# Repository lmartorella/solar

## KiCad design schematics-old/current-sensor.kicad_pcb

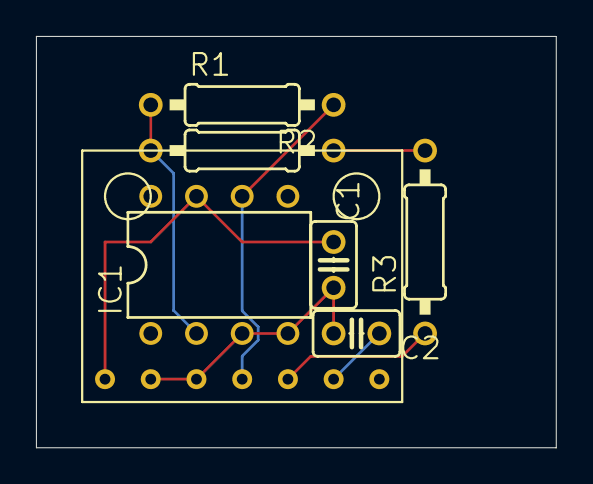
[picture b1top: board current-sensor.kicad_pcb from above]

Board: 2 copper layers, 28.9 x 22.9 mm, 7 parts (0 on the bottom side), 7 nets.

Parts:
C1: 100n; C025-025X050
C2: 1u; C025-025X050
IC1: 741P; DIL08
R1: 81k; 0207_10
R2: 33k; 0207_10
R3: 39; 0207_10
U$1: LTC1966_MODULE

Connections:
+5V: C1.1, IC1.7, U$1.P$1
GND: C1.2, C2.2, IC1.3, IC1.4, U$1.P$2, U$1.P$3
unnamed: C2.1, U$1.P$6
unnamed: IC1.2, R1.1, R2.2
unnamed: IC1.6, R1.2, U$1.P$4
unnamed: R2.1, R3.2
unnamed: R3.1, U$1.P$5

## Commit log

2019-04-23 - Restructuring folders to split app from lib
2019-04-24 Moved solution out
2019-04-24 Refactored done and working
2019-04-26 - Refactoring with dll reflection load done
2019-05-15 - Removed sink tabs without UI - Added some inline doc on classes - Code cleanup
2019-05-16 - Refactoring the web server - Added default garden cfg writer - Moved samples and webapp outside web code - Code simplification - Moved plotly and require to npm - Converted server code back to JS
2019-05-17 - Documenting
2019-07-03 - Added doc for ubean - Documenting
2020-03-23 - Added digital input simulator and tester device
2020-03-23 - Fixed serialization of JSON - Added node removal from simulator UI - Fixed UT
2020-03-23 - Fixed logger device - Added Initialized async task in Sinks
2020-03-23 - Implemented flow reading from bus
2020-03-24 - Implemented simulator too - Temp: update flow on web request
2020-03-25 - Fixed digio hw and c# sink driver
2020-03-28 Migrated to VS2019 and .NET 4.7.2
2020-03-31 - Admim mail support - Added packaging and install - Various web fixes
2020-04-04 - Added pump logger - Refactored the big Garden device file in sub classes
2020-04-04 - Fixed process management after restart
2020-04-05 - I18N of the web GUI
2020-04-07 - Protocol webserver/server reworked - .NET message separation samples/core
2020-04-07 - Completed localization
2020-04-07 - Better mail report (text) - Added Night Mode switch in the simulator - Added protocol debug
2020-04-07 - Completed loaded async reaction - Fixed daylight management after restart
2020-04-13 - Fixed JSON serialization ploymorphism - Fixed solar exception - Fixed i18n
2020-04-13 Merged schematics repo
2020-04-13 Current sensor
2020-04-13 - Sensor board
2020-04-13 - Fixed solar TCP open/close loop - Added logs to listen socket issue on raspbian (missing POLLINVALID check?)
2020-04-18 - i18n in garden
2020-04-21 Reworking disabled, to introduce suspend
2020-04-22 - Added suspended and reminder mail
2020-04-22 - Done
2020-04-26 - Integrated power usage reading in solar power to calculate Net Energy Meter
2020-04-27 - Added suspend/resume UI
2020-04-27 - WIP editor for cycles
2020-04-28 - Working editor for cycles
2020-04-29 - Resume from rain now updates the start time
2020-04-29 - Better implementation of remote set config
2020-04-29 - Hide Stop command if not running
2020-04-29 - Added login precheck
2020-04-29 - Fixed unhanlded
2020-04-29 - Fixed next cycle calculation after rain
2020-05-01 - Refactored zone names managements
2020-05-03 - Clean up immediate, now single cycle
2020-05-03 - Introduced optional sinks
2020-05-07 - Send restart mail with exception stack
2020-05-08 - Show current usage in W
2020-05-10 - Fixed deserialization buffer underflow management: TCP connection must be closed in that case to allow subsequent node access
2021-01-06 - SAMIL: New error code witnessed
2021-05-18 - More detailed errors about inverter packet errors
2021-05-22 - Support for 'broken' undocumented checksum?
2022-10-20 - Added scripts to aggregate yearly solar data
2023-05-14 - Folder renamed - Removed old PIC targets - Fixed UTs
2023-05-14 - Adding common service to replace the in-memory IPC pipe with the web gui
2023-05-14 - To test
2023-05-14 - Converted named pipe API to MQTT
2023-05-15 - Migrated webserver to mqtt
2023-05-16 - Extracted devices to different transformer processes
2023-05-17 - Removed obsoleted sink simulators - Correct bootstrap info for all applications
2023-05-17 - Readded UTs
2023-05-19 - Implemented solar protocol
2023-05-19 - Timeout and fixes
2023-05-20 Migrated ammeter
2023-05-20 Done flow and switch
2023-05-21 Migration to new API completed
2023-05-21 - Changed RPC protocol using the content-type
2023-05-23 - ES module conversion - Fixed MQTT connection management
2023-05-25 - Removed oxyplot
2023-05-26 - FIxed timeouts and protocol - Using managed client for persistent subscriptions
2023-05-26 - Fixed kill/restart, missing aggregated logs now
2023-05-28 - implemented logs
2023-05-28 - Fixed error management (500)
2023-05-28 - Fixed notification.json shared access - Fixed serialization types - Fixed exception if sink is down
2023-07-22 - Fixed exception in solar when offline
2023-08-01 - Adding partial results
2023-09-02 - Scanner working. - TODO TX pin timing on end-of-write
2023-09-02 - Fixed protocol of reg 0x3
2023-09-02 - Fixed addressing
2023-09-02 - Some rev eng on Sofar
2023-09-02 WIP .NET poll code
    - Removed backups
2023-09-02 - Missing timestamps
2023-09-02 - Added modbus mock server
2023-09-02 - WIP refactoring complete
2023-09-02 - Refactored InverterDevice, extracted UI MQTT interface
2023-09-02 - String resources
2023-09-02 - Installed Angular 16
2023-09-02 - Migrated admin
2023-09-02 - MIgrated garden
2023-09-03 - Migrated solar + plotly upgrade - Lazy load plotly
2023-09-03 - Migrated login and interceptor
2023-09-03 - Added favicon - Fixed build warnings
2023-09-03 - Better app/samples separation
2023-09-03 - FIxed security issue with secrets
2023-09-03 - Build/deploy optimization
2023-09-10 - Refolder
2023-09-10 - Cleanup
2023-09-10 - App/lib split complete
2023-09-12 - Imported common services API and impl
2023-09-13 - Migrated to .NET 7.0
2023-09-15 - Added lint
2023-09-15 - Implementing sample webapp and REST server
2023-09-15 - Added some style
2023-09-15 - Injectable base URL
2023-09-16 - Fixed port
2023-09-16 - Fixed CORS and status messages
2023-09-16 - Removed MQTT RPC dependency - Now UI uses regular topics
2023-09-16 - Using the /etc folder
2023-09-16 - Fixed error
2023-09-16 - Folder rename
2023-09-16 - Implemented ammeter modbus-to-MQTT bridge - Implemented mock for data
2023-09-18 - Added modbus configuration
2023-09-18 Embedde server code in lib
2023-09-18 - Added scope
2023-09-18 - Package json simplified
2023-09-24 - Fixed deps and module API
2023-09-24 - Empty
2023-09-25 - Converted schematics from Eagle to KiCad
2023-10-03 - Removed schematics, will use the reference design from the spreadsheet
2023-10-04 - Allow to disable devices from json
2023-10-07 - Support for modbus timeout
2023-10-07 - Stress tester to lower errors
2023-10-07 - Fixed errorResponse call, rtu id was missing - Fixed recovery of first byte
2023-10-07 - Wait for data flush in case of error
2023-10-07 - Explicit framework folder
2023-10-07 - Fixed lib link
2023-10-07 - Evidence of short resp
2023-10-08 - Fixed splitted messages
2023-10-08 - Fixed project folders
2023-10-08 - Simulator to check disconnections
2023-10-08 - Optimize traffic for missing ammeter
2023-10-08 - Fixed exception management in the main loop
2023-10-08 - Fixed exception due to modbus node down
2023-10-08 - Better error reporting
2023-10-08 - Tester for lost messages
2023-10-09 - More time for night mode
2023-10-09 - Properly using CancellationToken for timeouts
2023-10-09 - Disabled power today, algo not working
2023-10-09 - Show historical voltage data in chart
2023-10-09 - Calc and show grid voltage peak in UI
2023-10-09 - Fixed swapped i18n strings
2023-10-09 - Including the peak voltage in EOD notification as well
2023-10-10 - Coded, to be tested
2023-10-10 - Decoded counters, they are minutes, not charge
2023-10-10 - Removed wrong totals
2023-10-10 - Refinements
2023-10-10 - Rendering new non-fault states
2023-10-10 - More specific state about total data loss due to timeout
2023-10-10 - Properly supporting off mode in UI too
2023-10-10 - Added the simulator
2023-10-10 - Faster startup
2023-10-10 - Fixed mgmnt of totalloss (night)
2023-10-10 - Get rid of wrong charge
2023-10-10 - Removed total energy from UI and notifications
2023-10-10 - Fixed merge
2023-10-10 - Fix parsing CSV from it
2023-10-11 - Fixed kill message and Ctrl-C
2023-10-14 - Annotated some info from other projects
2023-10-15 - Verified
2023-10-15 - Restored total energy
2023-10-15 - Lint
2023-10-16 - Standalone build
2023-10-16 - Added support for historical day
2023-10-22 - Added queue support for multiple accesses - Added timeout (500ms) - Fixed debugging port
2023-10-22 - FIxed sending timeout in case of broken responses too
2023-10-22 - Added WDT for queue stuck
2023-10-23 - Fixed exception for malformed messages: https://github.com/Apollo3zehn/FluentModbus/pull/101
2023-10-23 - Fixed management of FluentModbus timeout with disconnection (the channel is internally closed) - Support for RTU timeout through modbus error
2023-10-23 - Refactor: extracted notification sender
2023-10-23 - Fixed night mode responding also to gateway down
2023-10-24 - Extracted bridge class
2023-10-24 - Correct platformio folders
2023-10-24 - Embedded telnet stream
2023-10-24 - Configuration for RTU pins
2023-10-24 - Moved to https://github.com/lmartorella/esp-modbus-bridge
2023-10-28 - Reimport Sofar recovery code from library
2023-11-02 - Trying reconnect, but it seems to be already implemented in the framework
2023-11-05 - Removed mDNS for esp32 - Moved esp8266 on master, MR merged but not tagged yet
2023-11-05 - Tagged esp-modbus-bridge
2023-11-05 - Reimported Sofar specific code
2023-11-05 - Renamed
2023-11-05 - Upgraded sample to pic-modbus lib
2023-11-08 - Fixed error management and using a shorter timeout in esp bridge - Cleanup - Improved serial mock to test 0x90 and timeout cases
2023-11-08 - Trying to fix splitter packets issue
2023-11-08 - Tested OK on ESP8266
2023-11-08 - Some cleanup
2023-11-08 - Preparing multi-channel support, modbus API side
2023-11-11 - Added test poller
2023-11-12 - Two analog channels, multiplexed
2023-11-14 - Fixed period sampling, independent on caller
2023-11-14 - Added calibration data + modbus API
2023-11-19 - Power saving
2023-11-26 - Removed calibration, to move to a separate branch
2023-11-26 - Reduced chatty logs during night
2023-11-28 - Tested OK
2023-11-30 - Added PIC specific bridge
2023-12-02 - Working
2023-12-02 - Adapted new PIC module
2023-12-03 - Added power logger TCP modbus
2024-04-18 - Renamed to avoid clash with inverter (device) state
2024-04-18 - CSV with getters
2024-04-18 - Passing detailed state args to all services
2024-04-18 - Fixed build, completed CSV aggregation
2024-04-26 - Fixed CSV compatibility
2024-04-27 - Avoid storing zeroed fault bits in normal WAIT/CHK operations
2024-04-28 - Added tests for re-aggregate old DBs
2024-06-11 - Fixed when mqtt server is IPV4 only
2024-06-17 - Aligned to MS extensions standard
2024-06-19 - Removed sendMailErr
2024-06-19 - Removed support to log on file
2024-06-23 - WIP
2024-06-23 - Refactored EnqueueStatusUpdate to be a stateless API
2024-06-23 - Removed HTML mail support
2024-06-29 - Fixed localhost IP - Added support for RCP - Made notification calls as full RPC
